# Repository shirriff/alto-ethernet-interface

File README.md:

# Alto Ethernet Interface

This project is an interface / gateway from the Xerox Alto's 3 Mb/s Ethernet
to the outside world.
The software runs on a [BeagleBone Black](http://beagleboard.org/bone) single-board Linux computer and uses a simple interface board (shield) to interface with the Alto's Ethernet.
This system makes use of the 
IFS file server software from [Living Computers Museum+Labs](http://livingcomputers.org).

## Background

Xerox PARC invented Ethernet in the 1970s, implementing 3 MB/s Ethernet on the Xerox Alto.
This was before TCP/IP and Xerox developed a network protocol called PUP (PARC Universal Packet) to run on Ethernet.
Xerox also built the IFS (Interim File Server), server software to support ftp, network boot, network disk copying, network services, gateways, and so forth.

The 3 MB/s Ethernet system consisted of several pieces.
A network interface board inside the Alto generated TTL signals.
The network itself consisted of a coaxial cable.
An external transceiver box translated between TTL signals and signals on the coaxial cable.
The TTL signals between the Alto and the transceiver consisted of the data from the Alto to the network, data to the Alto from the network, and a collision detection signal.

## Details of the interface

To hook the Alto up to a modern network, this project has several pieces:

 * A BeagleBone shield that interfaces to the Alto's Ethernet.
 * Gateway software on the BeagleBone to read/write packets.
 * The IFS file server running on the BeagleBone.
 
The BeagleBone processor includes two microcontrollers called PRUs.
This interface runs code on a PRU to send and receive the Ethernet data.
A C program communicates with the PRU and sends/receives the data locally
over UDP.
Finally, IFS also uses UDP to send/receive the packets, allowing the Alto to
communicate with IFS.

### The shield

The interface board plugs into the BeagleBone and simply translates signal
levels between the BeagleBone and the Alto.
A schematic and PCB design were created in KiCad, in the *board* directory.

### The Beaglebone software

 * The PRU code. This is written in C and is compiled using TI's Code Composer Studio.
 * The C gateway code.
 * The device tree overlay file, which sets the BeagleBone's pins correctly to communicate with the interface board.

The source code is in the *src* directory and pre-built binaries ready to install are in the *build* directory.

### IFS
 
The IFS software from [Living Computers Museum+Labs](http://livingcomputers.org).
This software is in C#. It can run on the BeagleBone using Mono.

The original IFS repository is [https://github.com/livingcomputermuseum/IFS](here://github.com/livingcomputermuseum/IFS).
My version of IFS with modified UDP support is [https://github.com/shirriff/IFS](https://github.com/shirriff/IFS).

## Installation

To configure a BeagleBone with this software, see [build/README.md](build/README.md).

## Use

Connect the Ethernet cable from the cape (i.e. the top board) to the Alto.
Boot the BeagleBone.
The 4 LEDs on the BeagleBone should flash randomly for about 35 seconds.
Then the LEDs should go out for a few seconds.
Then the first and last LEDs should blink briefly every second.

On the Alto, hold down backspace and apostrophe. Press the reset button on the back of the keyboard. Continue holding down backspace and apostrophe for a couple seconds until the cursor changes to a box of dots.
While this is happening, the first, second and fourth LED should be flashing a lot, indicating network traffic.
Hopefully the Alto will boot to the "Net Executive".
From here, type a question mark to list commands.
Type `astroroids` [sic] to boot the Asteroids game.
Type `ftp` for FTP. Note: it will hang with a two-box cursor if you don't have a disk running.
```
login test
open 1#
list *
```

You should be able to ssh into the BeagleBone as 192.168.4.5 if necessary.

## Notes

LEDS:
* 0 (Left): sending packet to Alto
* 1: received packet from Alto
* 2: timeout (5 seconds with no activity)
* 3: select loop (gateway alive)

(To create IFS.tgz: tar -czvf IFS.tgz IFS)
To check systemd: `systemctl status alto-gateway.service` (or alto-ifs.service)
Also look in /var/log/syslog for errors

For background on the BeagleBone, see my articles on the [BeagleBone PRU](http://www.righto.com/2016/08/pru-tips-understanding-beaglebones.html) and [PRU C compiler](http://www.righto.com/2016/09/how-to-run-c-programs-on-beaglebones.html).

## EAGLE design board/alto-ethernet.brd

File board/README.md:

# Instructions for building the v3 board

The v3 board works as is. This board fixes a missing trace in v2. The v1 board is not software compatible
with the v2/v3 coards.

The board was designed with KiCad. This directory contains the KiCad files.
The board can be ordered from OshPark [here](https://oshpark.com/shared_projects/q9WVjQhn).

## Materials

* 7438 open-collector NAND gate.
* 2 x [2x23 Male Headers](https://www.adafruit.com/product/2076)
* C2, C3: 2 x [0.1uF ceramic capacitor](https://www.adafruit.com/product/753)
* R3: 120 ohm resistor
* R4: 330 ohm resistor
* Ethernet connector: through-hole, PCB mount RJ45
* DB25 male to RJ45 female modular adapter kit ([ADM-25M8-BK](http://www.frys.com/product/1544923))
* Ethernet cable
* BeagleBone Black + power supply + network connection (e.g. Apple Thunderbolt to Ethernet)

Note: R1/R2/C1 in the middle of the board are unused. They were provided in case a pullup/down was needed.

## DB25 connector wiring
 * 3 Blue
 * 16 Orange

 * 8 Red
 * 20 Green

 * 12 Yellow
 * 24 Black

 * 13 White
 * 25 Brown

Insert pins from back. Pin 1 is left on the wider side. Push pins in until they click.
You can twist the pairs of wires together if you want.

<pre>
W Y . . . R . . . . L . .
 N K . . . G . . . O . .
</pre>
(L = blue, N = brown, K = black)

## Testing

Output signal to Alto can be measured across pins 7 and 3 of the IC (pin 7 = ground). When connected to Alto, signal should be idle low (0.2V), pulsing to 3.5V. Can be a bit of overshoot, but shouldn't be ringing.
When disconnected from Alto, signal should go between 0V and 5V.

Input signal from Alto can be measured across the right hand side of a resistor. Signal should be idle high (2.2V) pulsing to 0V.

## LEDS

0 = top, 3 = closest to Ethernet port.
0 and 3 should flash every 2 seconds for Breath-of-life packet.
Others should flash during network boot or other network traffic.
If LED 0 is stuck on, reboot the BeagleBone. (There's something wrong with the gateway.)

At the end of a disk boot, LED 1 should flash a couple times (as the Alto does a couple network requests).

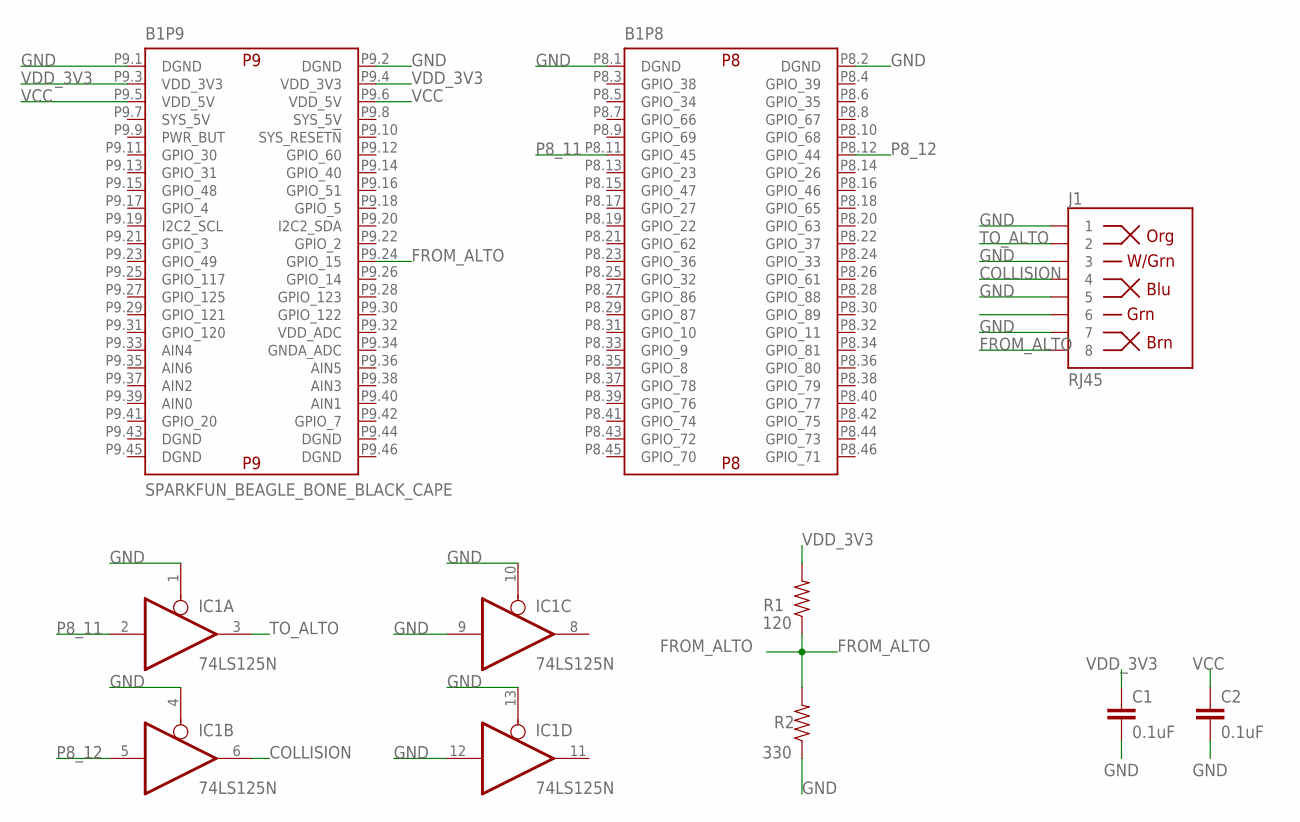
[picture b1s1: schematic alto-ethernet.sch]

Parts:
B1: SPARKFUN_BEAGLE_BONE_BLACK_CAPE; BEAGLE_BONE_BLACK_CAPE
C1, C2: 0.1uF; CAP-PTH-SMALL-KIT
IC1: 74LS125N; DIL14
J1: RJ45; RJ45-8
R1: 120; AXIAL-0.3
R2: 330; AXIAL-0.3

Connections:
COLLISION: IC1.6 (O), J1.4
FROM_ALTO: B1.P9.24 (GPIO_15), J1.8, R1.P$1 (1), R2.P$2 (2)
GND: B1.P8.1 (DGND), B1.P8.2 (DGND), B1.P9.1 (DGND), B1.P9.2 (DGND), C1.2, C2.2, IC1.1 (OE), IC1.4 (OE), IC1.7 (GND), IC1.9 (I), IC1.10 (OE), IC1.12 (I), IC1.13 (OE), J1.1, J1.3, J1.5, J1.7, R2.P$1 (1)
P8_11: B1.P8.11 (GPIO_45), IC1.2 (I)
P8_12: B1.P8.12 (GPIO_44), IC1.5 (I)
TO_ALTO: IC1.3 (O), J1.2
VCC: B1.P9.5 (VDD_5V), B1.P9.6 (VDD_5V), C2.1, IC1.14 (VCC)
VDD_3V3: B1.P9.3 (VDD_3V3), B1.P9.4 (VDD_3V3), C1.1, R1.P$2 (2)

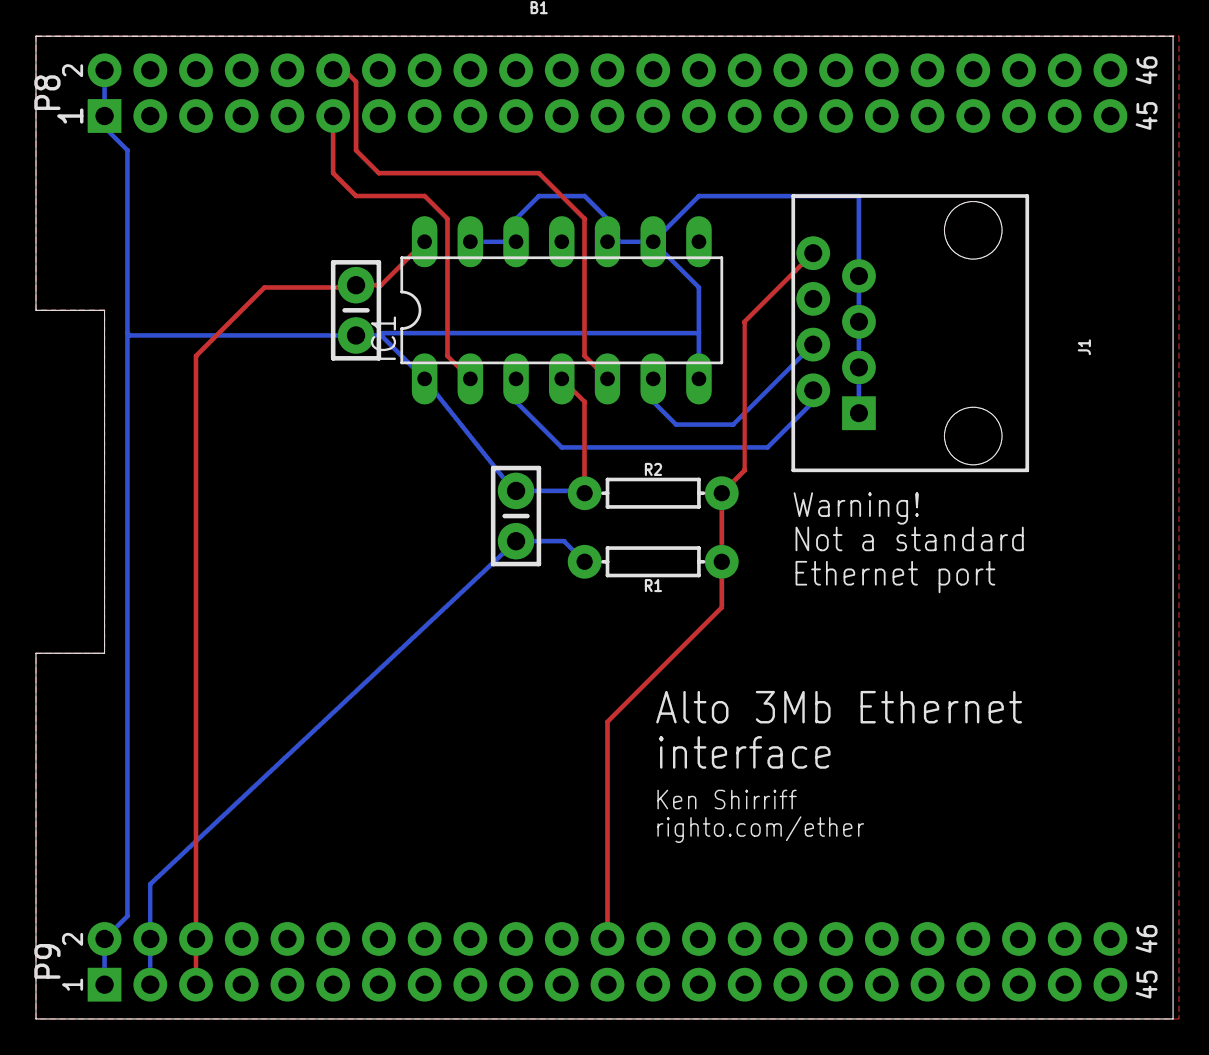
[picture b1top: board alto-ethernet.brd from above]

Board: 2 copper layers, 63.2 x 54.6 mm, 7 parts (0 on the bottom side), 8 nets.

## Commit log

2017-10-12 Initial commit.
2017-10-13 Interface board design.
2017-10-13 Add built files
2017-10-13 Replace ethertext.bin with working version.
2017-10-18 Fix race condition
2017-10-24 Updated binary files
2017-10-27 Fix PUP checksum bug (drop Ether CRC from received packet). Clean up code.
2017-10-27 etherNet: add logging, verbose options. Clean up code.
2017-10-27 Rename etherNet.c to gateway.c
2017-11-08 Change synchronization model: read and write buffers owned by PRU or ARM Also remove delay in starting read; was dropping packets received just after write.
2017-11-09 Fix bug with double-clearing events.
2017-12-05 Working version.
2017-12-13 Schematic of board.
2017-12-20 Add version 2 of the board.
2018-01-08 Update README, indicating boardv2 is obsolete
2018-01-08 Add v3 of board design.
2018-01-08 Rename boardv2 to board. Replace the Eagle version with the KiCad version
2018-01-08 Rename directories
2018-01-26 Changes to support v2/v3 board.
    The driver chip in the v2/v3 board inverts polarity, so the gateway code
    needs to flip polarity of the outgoing data and collision signal.
    ethertext.bin is updated with the new code.
    Note: to use the v1 board, you need to use ethertext.bin.v1.
2018-01-26 Update README with v3 info.
2018-02-05 Add instructions for using disk image.
2018-02-05 Add note on SD installation.
2020-05-28 Fix pin number typo.
2020-05-28 Fix pin typo

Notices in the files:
parts and their libraries:
SparkFun-Boards: Licensing: Creative Commons ShareAlike 4.0 International - https://creativecommons.org/licenses/by-sa/4.0
